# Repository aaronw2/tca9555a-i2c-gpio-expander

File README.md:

A TCA9555A i2c GPIO expander board

I am doing an ESP32 Wrover based design and I need additional GPIO pins to
monitor 10 hall effect sensors. I want to generate an interrupt whenever one
of them is triggered. This board is designed so that I can plug my existing
ribbon cable directly into J2 (with the pins installed on the back of the
board) with J3 providing the rest of the pins.

J1 provides power, 2 grounds, interrupt, i2c SDA and i2c SCL signals.
The three JP pads can be filled in with solder to choose the address.
Multiple boards can be chained together, though J1 is not fully set up
or this. In this case, the resistor network RN1 should only be installed
on the last board in the chain. The TCA9555A is capable of 400KHz i2c.
It can generate an interrupt whenever one of the unmasked pins changes state.

Note that A0, A1 and A2 default to 1.  To change the address to zero, short
the appropriate address jumper.

A datasheet on the GPIO expander can be found here:
http://www.ti.com/lit/ds/symlink/tca9555.pdf

Please direct any questions or comments to Aaron Williams <aaron.w2@gmail.com>

Copyright (C) 2018 by Aaron Williams

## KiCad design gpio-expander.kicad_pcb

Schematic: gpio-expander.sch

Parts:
C1: 1uF; C_0603_1608Metric
C2, C3, C4: 10uF; C_0805_2012Metric
FID1, FID4: FIDUCIAL_1MM; Fiducial_1mm_Dia_2.54mm_Outer_CopperTop
FID2, FID3: FIDUCIAL_1MM; Fiducial_1mm_Dia_2.54mm_Outer_CopperBottom
J1: Conn_01x10; Pin_Header_Angled_1x10_Pitch2.54mm
J2: Conn_02x07_Odd_Even; Pin_Header_Angled_2x07_Pitch2.54mm
J3: Conn_02x04_Odd_Even; Pin_Header_Angled_2x04_Pitch2.54mm
MH1, MH2: MountingHole; MountingHole_2.5mm
RN1: R_Pack02; R_Array_Concave_2x0603
RN2: 10k; R_Array_Convex_4x0603
SW1: SW_DIP_x06; SW_DIP_SPSTx06_Slide_GrayHill_97C06_W4.5mm_P1.27mm
U1: TCA9555DBT; TSSOP-24_4.4x7.8mm_Pitch0.65mm

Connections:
+3V3: C1.1, C2.1, C3.1, C4.1, J1.5, J1.10, J2.1, J3.1, SW1.1, SW1.2, SW1.3, SW1.4, SW1.5, SW1.6, U1.24 (VCC)
/A0: RN2.3, SW1.9, U1.21 (A0)
/A1: RN2.2, SW1.8, U1.2 (A1)
/A2: RN2.1, SW1.7, U1.3 (A2)
/P00: J2.3, U1.4 (P00)
/P01: J2.4, U1.5 (P01)
/P02: J2.5, U1.6 (P02)
/P03: J2.6, U1.7 (P03)
/P04: J2.7, U1.8 (P04)
/P05: J2.8, U1.9 (P05)
/P06: J2.9, U1.10 (P06)
/P07: J2.10, U1.11 (P07)
/P10: J2.11, U1.13 (P10)
/P11: J2.12, U1.14 (P11)
/P12: J3.3, U1.15 (P12)
/P13: J3.4, U1.16 (P13)
/P14: J3.5, U1.17 (P14)
/P15: J3.6, U1.18 (P15)
/P16: J3.7, U1.19 (P16)
/P17: J3.8, U1.20 (P17)
/SCL: J1.3, J1.8, RN2.5, U1.22 (SCL)
/SCL_PU: RN2.4, SW1.10
/SDA: J1.4, J1.9, RN1.2, U1.23 (SDA)
/SDA_PU: RN1.3, SW1.11
/~INT: J1.2, J1.7, RN1.1, U1.1 (~INT)
/~INT_PU: RN1.4, SW1.12
GND: C1.2, C2.2, C3.2, C4.2, J1.1, J1.6, J2.2, J2.13, J2.14, J3.2, RN2.6, RN2.7, RN2.8, U1.12 (GND)

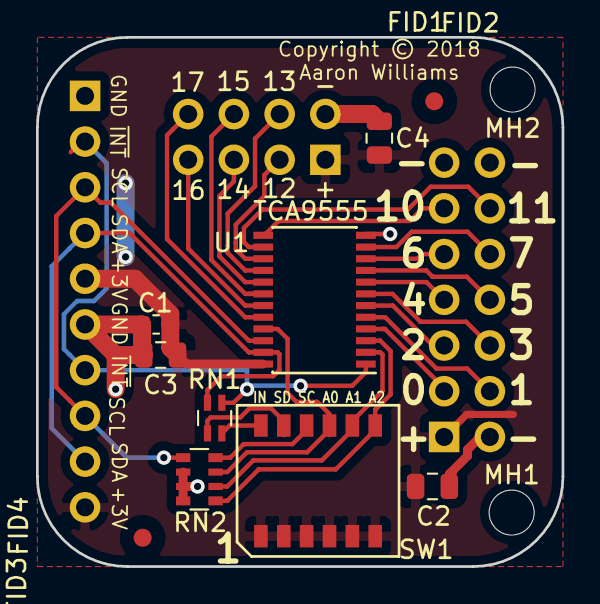
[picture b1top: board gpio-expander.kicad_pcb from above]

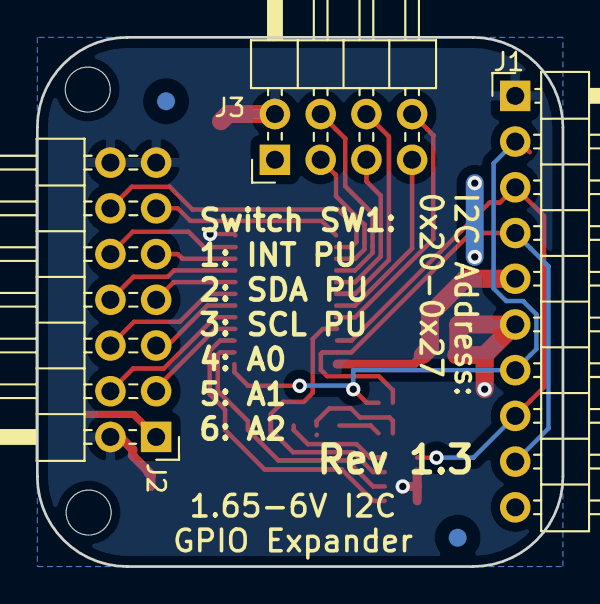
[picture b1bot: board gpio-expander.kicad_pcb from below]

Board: 2 copper layers, 29.2 x 29.4 mm, 17 parts (3 on the bottom side), 27 nets.

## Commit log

2018-09-19 Initial checkin
2018-09-19 Added gerber files
2018-10-02 Rev 1.2
2018-10-03 - Added a dip switch for setting the address and termination - Added mounting holes - Changed J1 to a 10-pin connector with all pins duplicated for stacking - Minor cleanup - Updated README
2018-10-11 Fixed solder mask clearance.
2018-10-12 Fixed the footprint to not use a git library.
2018-10-12 Minor change. Made trace 45 degree instead of 90 degrees.

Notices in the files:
gpio-expander.kicad_pcb:
Copyright © 2018
